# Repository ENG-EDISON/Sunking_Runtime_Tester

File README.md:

# Sunking_Runtime_Tester
This repository contains the PCB schematics for runtime tester

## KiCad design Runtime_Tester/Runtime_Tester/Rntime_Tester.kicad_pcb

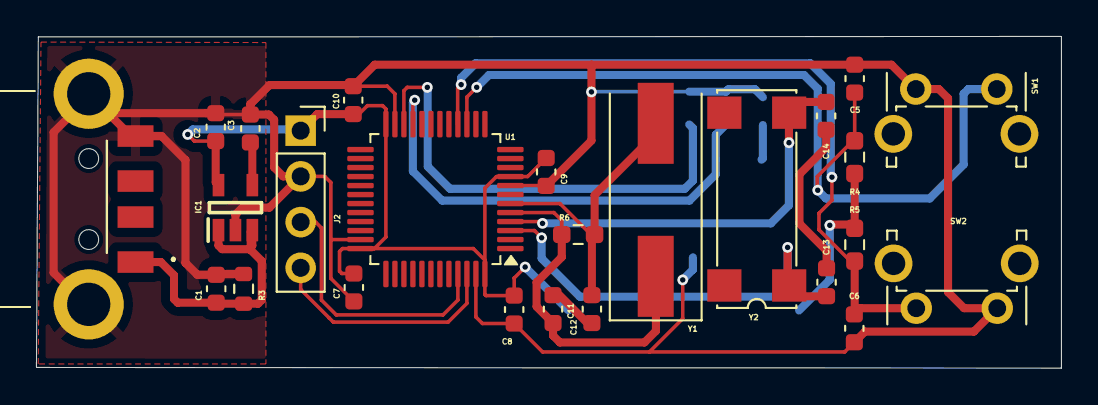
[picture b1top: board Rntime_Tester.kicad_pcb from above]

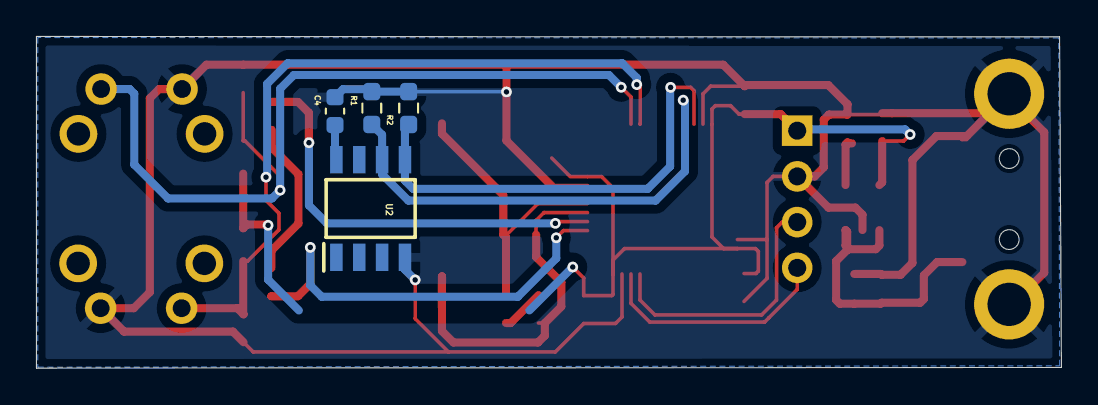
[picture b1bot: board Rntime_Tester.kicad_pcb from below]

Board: 2 copper layers, 56.9 x 18.4 mm, 29 parts (4 on the bottom side), 17 nets.

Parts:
C1, C2: 2.2uF; C_0603_1608Metric
C3: 22nF; C_0603_1608Metric
C4: 1.1uF; C_0603_1608Metric
C5, C6: 10uF; C_0603_1608Metric
C7, C8, C9, C10: 100nF; C_0603_1608Metric
C11, C12, C13, C14: 20pF; C_0603_1608Metric
IC1: RT9193-33GB; SOT94P279X130-5N
J2: Oled display; PinSocket_1x04_P2.54mm_Vertical
J3: 48037-2100; 480372100
R1, R2: 10K; R_0603_1608Metric_Pad0.98x0.95mm_HandSolder
R3: 100k; R_0603_1608Metric
R4, R5: 10k; R_0603_1608Metric_Pad0.98x0.95mm_HandSolder
R6: 1M; R_0603_1608Metric_Pad0.98x0.95mm_HandSolder
SW1: Reset; SW_Tactile_SPST_Angled_PTS645Vx39-2LFS
SW2: Continue; SW_Tactile_SPST_Angled_PTS645Vx39-2LFS
U1: STM32F103C8Tx; LQFP-48_7x7mm_P0.5mm
U2: CAT24C256; SOIC127P600X175-8N
Y1: Crystal; Crystal_SMD_HC49-SD
Y2: Crystal; Crystal_SMD_SeikoEpson_MA406-4Pin_11.7x4.0mm

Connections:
+3.3V: C2.1, C7.1, C8.1, C9.1, C10.1, IC1.5 (VOUT), J2.1, R4.1, R5.1, U1.9 (VDDA), U1.24 (VDD), U1.36 (VDD), U1.48 (VDD)
+3V3: C4.1, U2.8 (VCC)
+5V: C1.1, IC1.1 (VIN), IC1.3 (EN), J3.1, R3.1
/Continue: C6.1, R5.2, SW2.2, U1.16 (PA6)
/EEPROM_SCL: R1.2, U1.21 (PB10), U2.6 (SCL)
/EEPROM_SDA: R2.2, U1.22 (PB11), U2.5 (SDA)
/OSC_IN: C11.1, R6.1, U1.5 (PD0), Y1.1
/OSC_OUT: C12.2, R6.2, U1.6 (PD1), Y1.2
/Oled_SCL: J2.3, U1.45 (PB8)
/Oled_SDA: J2.4, U1.46 (PB9)
/PC14: C13.1, U1.3 (PC14), Y2.1
/PC15: C14.2, U1.4 (PC15), Y2.2
/Reset: C5.1, R4.2, SW1.2, U1.15 (PA5)
GND: C1.2, C2.2, C3.2, C4.2, C5.2, C6.2, C7.2, C8.2, C9.2, C10.2, IC1.2 (GND), J2.2, J3.4, J3.MH1, J3.MH2, R1.1, R2.1, R3.2, SW1.1, SW2.1, U1.8 (VSSA), U1.23 (VSS), U1.35 (VSS), U1.47 (VSS), U2.4 (GND)
unnamed: C11.2, C12.1
unnamed: C13.2, C14.1
unnamed: C3.1, IC1.4 (BP)

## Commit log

2024-10-14 PCBA and datasheets
2024-10-14 editted
2024-10-16 added more components
2024-10-18 Organised the schematics
2024-10-18 added traces
2024-10-19 more design
2024-10-19 schematic not working
2024-10-22 pcb routing
2024-10-22 routing
2024-10-22 delete
2024-11-18 Added error correction
